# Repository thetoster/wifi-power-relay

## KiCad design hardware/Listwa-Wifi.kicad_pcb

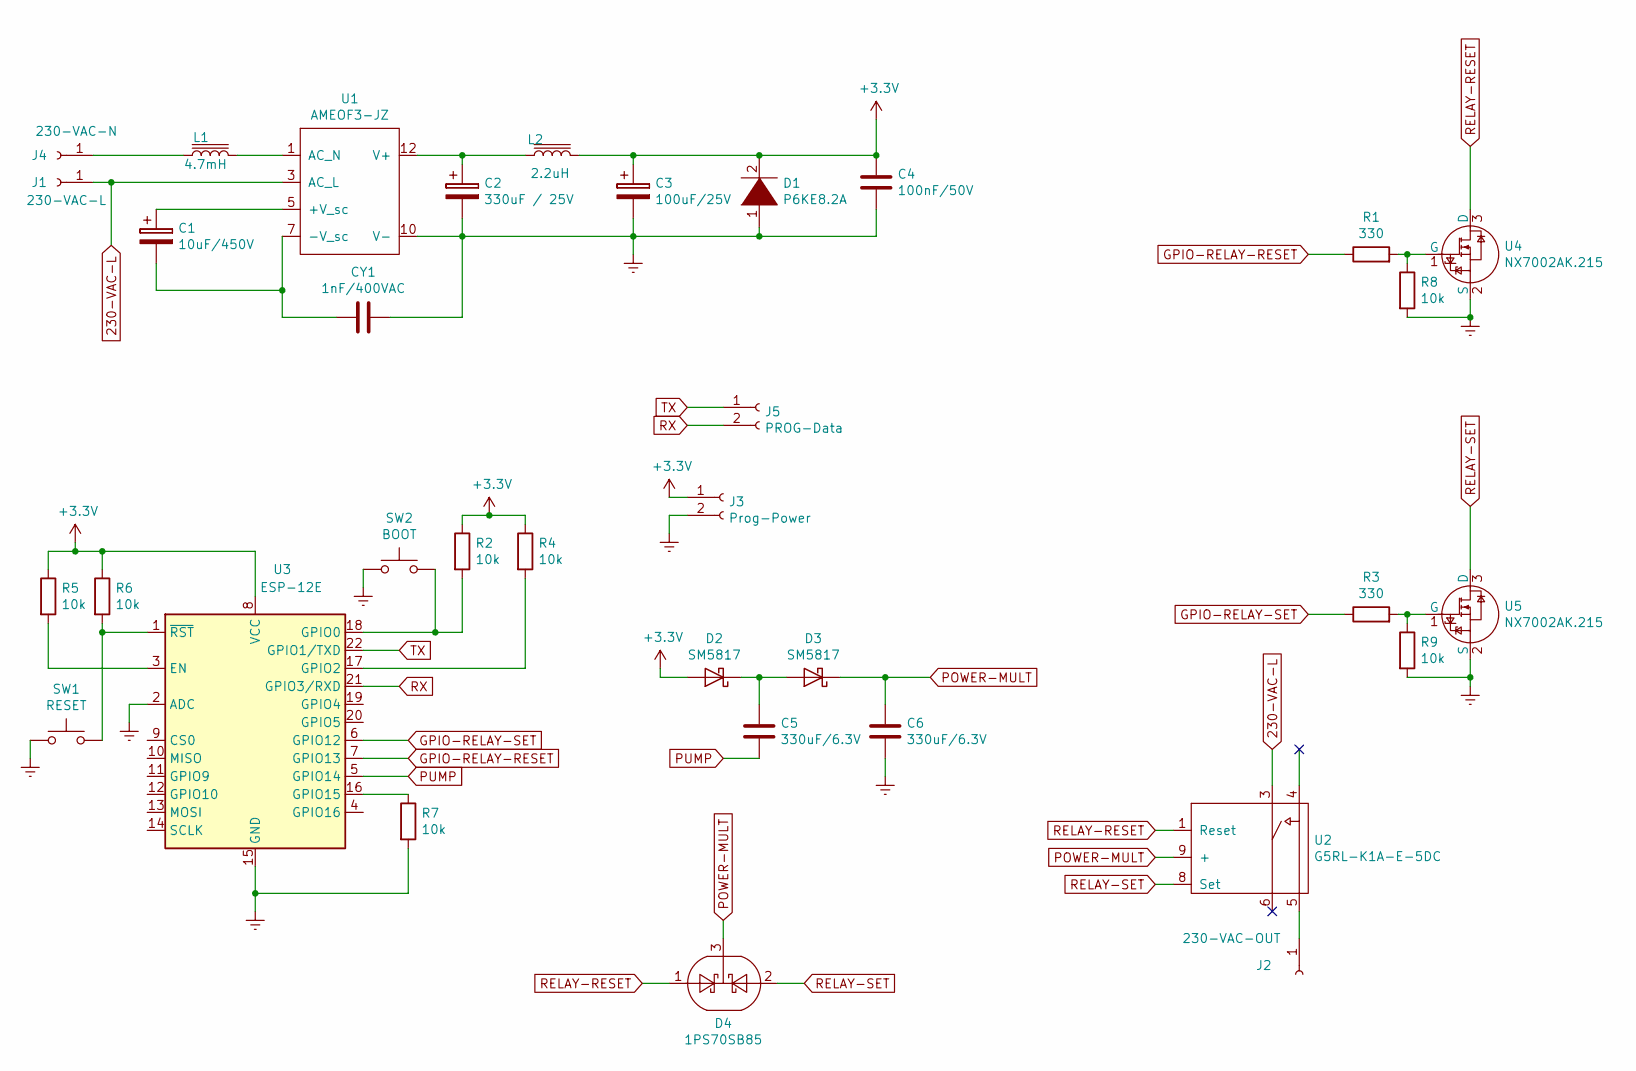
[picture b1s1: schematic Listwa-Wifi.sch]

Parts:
C1: 10uF/450V; CP_Radial_D10.0mm_P5.00mm
C2: 330uF / 25V; CP_Elec_8x10
C3: 100uF/25V; CP_Elec_6.3x7.7
C4: 100nF/50V; C_0603_1608Metric
C5, C6: 330uF/6.3V; CP_Elec_6.3x7.7
CY1: 1nF/400VAC; C_Disc_D4.3mm_W1.9mm_P5.00mm
D1: P6KE8.2A; D_DO-41_SOD81_P7.62mm_Horizontal
D2, D3: SM5817; D_MELF
D4: 1PS70SB85; SOT-323_SC-70
J1: 230-VAC-L; PAD-5x5mm
J2: 230-VAC-OUT; PAD-5x5mm
J3: Prog-Power; PinHeader_1x02_P2.54mm_Vertical
J4: 230-VAC-N; PAD-5x5mm
J5: PROG-Data; PinHeader_1x02_P2.54mm_Vertical
L1: 4.7mH; COIL1010-4.7
L2: 2.2uH; R_Axial_DIN0204_L3.6mm_D1.6mm_P1.90mm_Vertical
R1, R3: 330; R_0603_1608Metric
R2, R4, R5, R6, R7, R8, R9: 10k; R_0603_1608Metric
SW1: RESET; TACTM-34N-F
SW2: BOOT; TACTM-34N-F
U1: AMEOF3-JZ
U2: G5RL-K1A-E-5DC; OMRON G5RL-K1A-E-5DC
U3: ESP-12E
U4, U5: NX7002AK.215; SOT-23

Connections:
230-VAC-L: J1.1, U1.3 (AC_L), U2.3
+3V3: C3.1, C4.1, D1.2 (A), D2.2 (A), J3.1, L2.2, R2.1, R4.1, R5.1, R6.1, U3.8 (VCC)
Earth: C2.2, C3.2, C4.2, C6.2, CY1.1, D1.1 (K), J3.2, R7.2, R8.2, R9.2, SW1.1, SW2.1, U1.10 (V-), U3.2 (ADC), U3.15 (GND), U4.2 (S), U5.2 (S)
GPIO-RELAY-RESET: R1.1, U3.7 (GPIO13)
GPIO-RELAY-SET: R3.1, U3.6 (GPIO12)
unnamed: C1.1, U1.5 (+V_sc)
unnamed: C1.2, CY1.2, U1.7 (-V_sc)
unnamed: C2.1, L2.1, U1.12 (V+)
unnamed: C5.1, D2.1 (K), D3.2 (A)
unnamed: J2.1, U2.5
unnamed: J4.1, L1.1
unnamed: L1.2, U1.1 (AC_N)
unnamed: R1.2, R8.1, U4.1 (G)
unnamed: R2.2, SW2.2, U3.18 (GPIO0)
unnamed: R3.2, R9.1, U5.1 (G)
unnamed: R4.2, U3.17 (GPIO2)
unnamed: R5.2, U3.3 (EN)
unnamed: R6.2, SW1.2, U3.1 (~RST)
unnamed: R7.1, U3.16 (GPIO15)
POWER-MULT: C6.1, D3.1 (K), D4.3, U2.9 (+)
PUMP: C5.2, U3.5 (GPIO14)
RELAY-RESET: D4.1, U2.1 (Reset), U4.3 (D)
RELAY-SET: D4.2, U2.8 (Set), U5.3 (D)
RX: J5.2, U3.21 (GPIO3/RXD)
TX: J5.1, U3.22 (GPIO1/TXD)

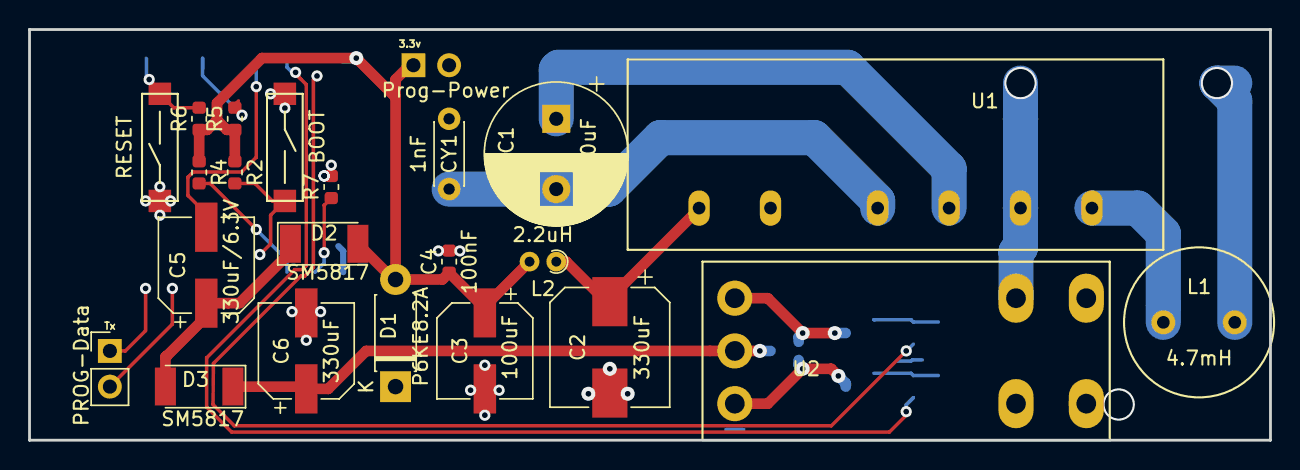
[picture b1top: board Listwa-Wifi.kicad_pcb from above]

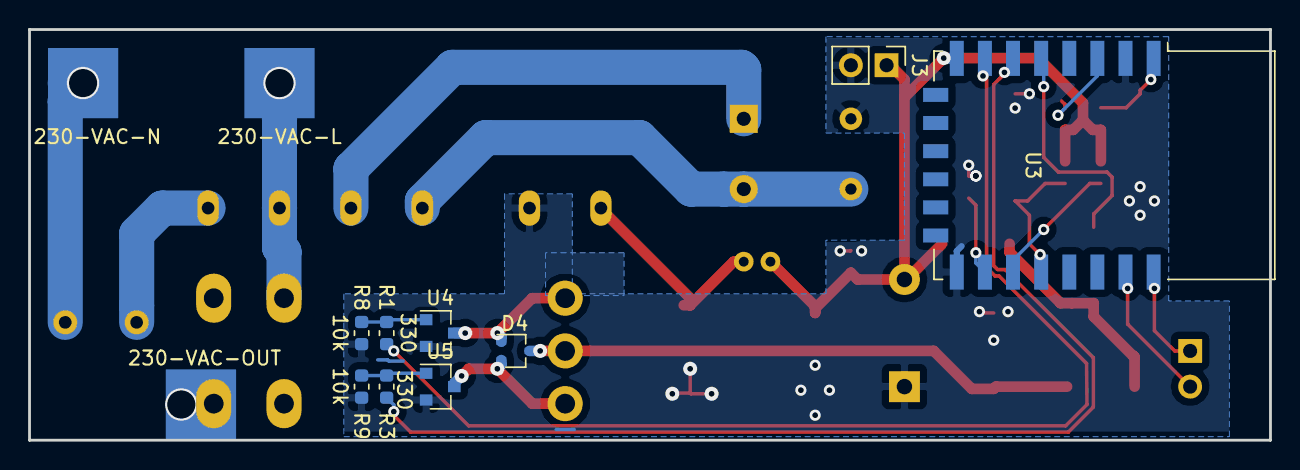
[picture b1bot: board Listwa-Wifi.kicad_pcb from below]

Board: 2 copper layers, 88.3 x 29.2 mm, 34 parts (12 on the bottom side), 25 nets.

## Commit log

2018-11-05 Add hardware
2018-11-05 Add holes on pads, better GND plane
2019-11-22 Some work with software, not stable
2019-11-28 Code cleanup & refactor
2019-12-02 Relay operational
2019-12-03 Little clenup
